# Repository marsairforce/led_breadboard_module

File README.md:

# A LED indicator module for breadboard development

I became frustrated at having to repeat the boring work of foraging parts, assembling, and then testing status LED circuits for breadboard development with digital logic circuits.

## The Problem

- Most microcontroller projects on a breadboard benefit from several LEDs to show status.
- LEDs operate at voltages lower than logic levels, so require current limiting resistors.
- LEDs typically draw about 10mA or more per LED. Sometimes it is not desirable to load the digital I/O pins from the microcontroller.
  - Quite often a single package device is not capable of sourcing the total current required for a lot of LEDs. For example a 74HC595 is typically capabale of sourcing or sinking up to 70mA. If all of their outputs are active the sum of their currents must not exceed this.
- If we use a simple current limiting resistor, we need to compute the value depending on the forward voltage of the LED and the desired voltage we are working with (today this is either 5V or 3.3V)

So in practice we would would want to set up some kind of buffer with current limiting resistors for the LEDs:

- some transistors and resistors
- or a driver IC like the ULN2803

The whole effort of building LEDs, driver circuits on a breadboard every time is error prone.

And it inconveniently takes up a lot of space on your breadboard.

So I set out to build a module that could be reused between projects.

- [Version 3](./doc/v3.md)
- [Version 2](./doc/v2.md)
- [Version 1](./doc/v1.md)

This project started of as what seemed like a simple activity but turned into a mechanism for a lot of learning.

See Also: [Transistor Theory](./doc/transistor_theory.md)

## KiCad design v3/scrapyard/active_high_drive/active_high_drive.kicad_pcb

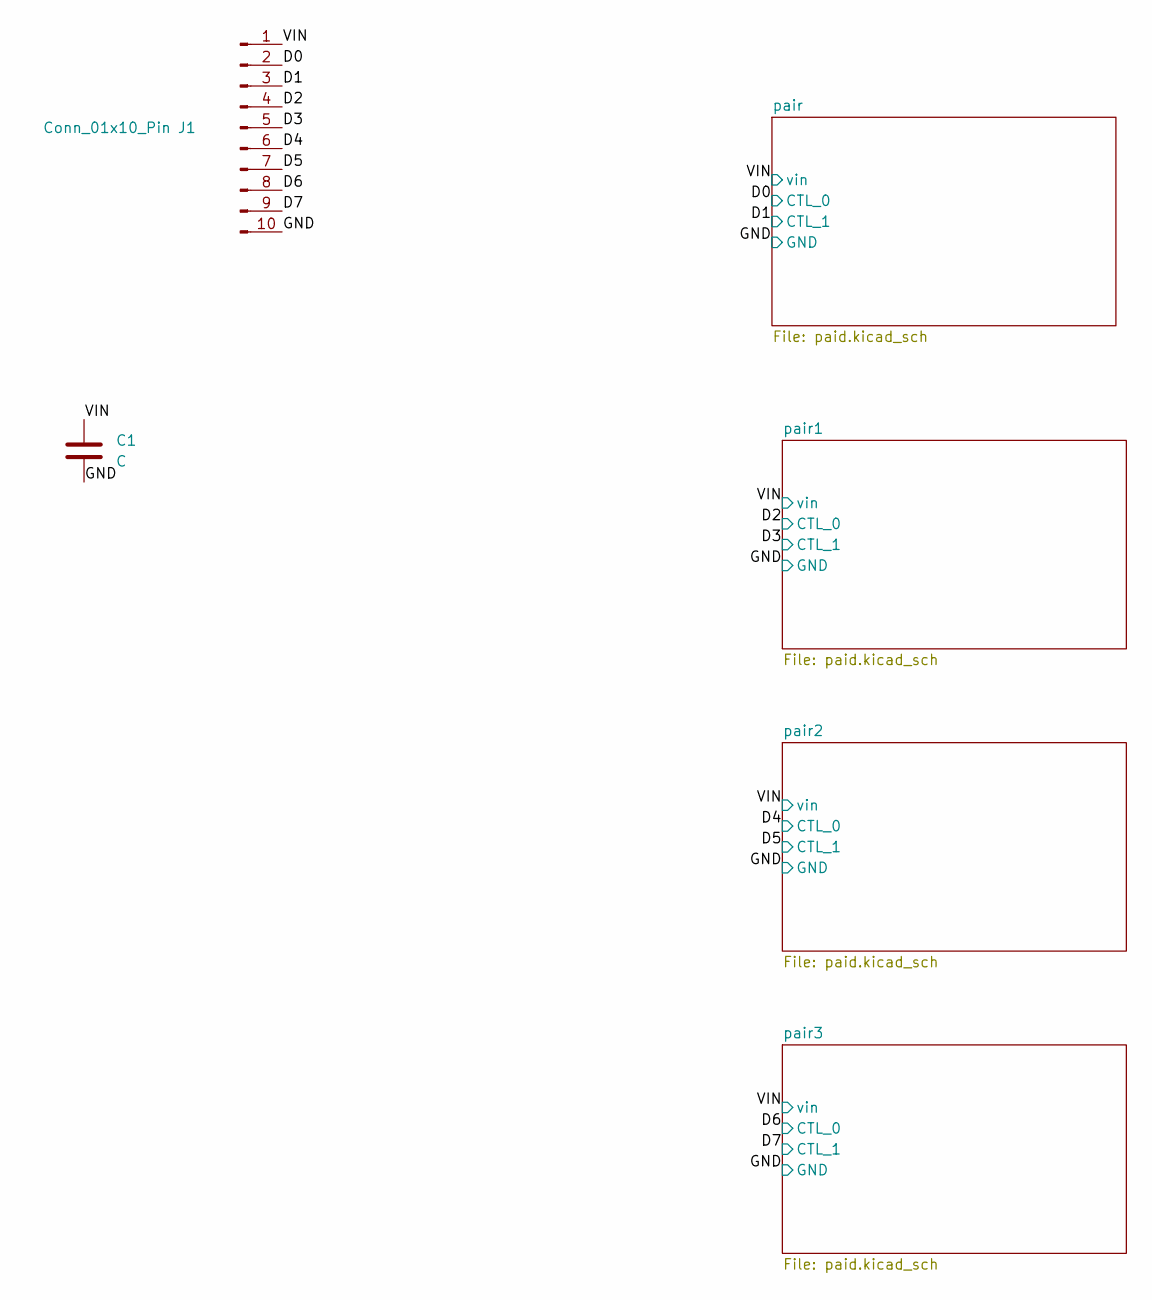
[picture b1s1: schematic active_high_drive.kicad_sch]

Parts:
C1: C; C_0603_1608Metric
J1: Conn_01x10_Pin; PinHeader_1x10_P2.54mm_Horizontal

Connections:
/D0: J1.2; also elsewhere on the board
/D1: J1.3; also elsewhere on the board
/D2: J1.4; also elsewhere on the board
/D3: J1.5; also elsewhere on the board
/D4: J1.6; also elsewhere on the board
/D5: J1.7; also elsewhere on the board
/D6: J1.8; also elsewhere on the board
/D7: J1.9; also elsewhere on the board
/GND: C1.2, J1.10; also elsewhere on the board
/VIN: C1.1, J1.1; also elsewhere on the board

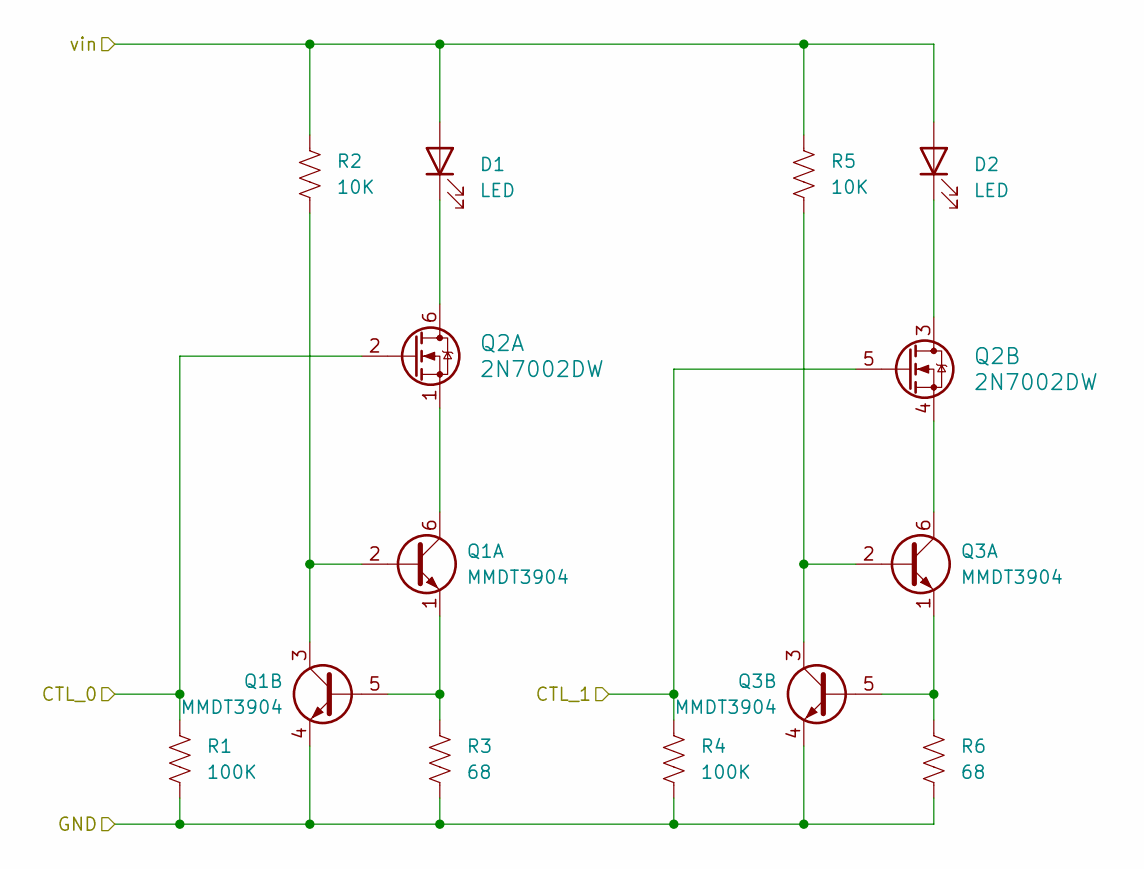
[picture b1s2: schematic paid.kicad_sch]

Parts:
D1, D2: LED; LED_0603_1608Metric
Q1, Q3: MMDT3904; SOT-363_SC-70-6
Q2: 2N7002DW; SOT-363_SC-70-6
R1, R4: 100K; R_0402_1005Metric
R2, R5: 10K; R_0402_1005Metric
R3, R6: 68; R_0402_1005Metric

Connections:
/D0: Q2.2 (G), R1.1; also elsewhere on the board
/D1: Q2.5 (G), R4.1; also elsewhere on the board
/GND: Q1.4 (E2), Q3.4 (E2), R1.2, R3.2, R4.2, R6.2; also elsewhere on the board
/VIN: D1.2 (A), D2.2 (A), R2.1, R5.1; also elsewhere on the board
unnamed: D1.1 (K), Q2.6 (D)
unnamed: D2.1 (K), Q2.3 (D)
unnamed: Q1.2 (B1), Q1.3 (C2), R2.2
unnamed: Q1.6 (C1), Q2.1 (S)
unnamed: Q1.1 (E1), Q1.5 (B2), R3.1
unnamed: Q2.4 (S), Q3.6 (C1)
unnamed: Q3.2 (B1), Q3.3 (C2), R5.2
unnamed: Q3.1 (E1), Q3.5 (B2), R6.1

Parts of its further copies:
D3, D4, D5, D6, D7, D8: LED; LED_0603_1608Metric
Q4, Q6, Q7, Q9, Q10, Q12: MMDT3904; SOT-363_SC-70-6
Q5, Q8, Q11: 2N7002DW; SOT-363_SC-70-6
R7, R10, R13, R16, R19, R22: 100K; R_0402_1005Metric
R8, R11, R14, R17, R20, R23: 10K; R_0402_1005Metric
R9, R12, R15, R18, R21, R24: 68; R_0402_1005Metric

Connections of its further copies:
/D2: Q5.2 (G), R7.1; also elsewhere on the board
/D3: Q5.5 (G), R10.1; also elsewhere on the board
/D4: Q8.2 (G), R13.1; also elsewhere on the board
/D5: Q8.5 (G), R16.1; also elsewhere on the board
/D6: Q11.2 (G), R19.1; also elsewhere on the board
/D7: Q11.5 (G), R22.1; also elsewhere on the board
/GND: Q4.4 (E2), Q6.4 (E2), Q7.4 (E2), Q9.4 (E2), Q10.4 (E2), Q12.4 (E2), R7.2, R9.2, R10.2, R12.2, R13.2, R15.2, R16.2, R18.2, R19.2, R21.2, R22.2, R24.2; also elsewhere on the board
/VIN: D3.2 (A), D4.2 (A), D5.2 (A), D6.2 (A), D7.2 (A), D8.2 (A), R8.1, R11.1, R14.1, R17.1, R20.1, R23.1; also elsewhere on the board
unnamed: D3.1 (K), Q5.6 (D)
unnamed: D4.1 (K), Q5.3 (D)
unnamed: D5.1 (K), Q8.6 (D)
unnamed: D6.1 (K), Q8.3 (D)
unnamed: D7.1 (K), Q11.6 (D)
unnamed: D8.1 (K), Q11.3 (D)
unnamed: Q4.2 (B1), Q4.3 (C2), R8.2
unnamed: Q4.6 (C1), Q5.1 (S)
unnamed: Q4.1 (E1), Q4.5 (B2), R9.1
unnamed: Q5.4 (S), Q6.6 (C1)
unnamed: Q6.2 (B1), Q6.3 (C2), R11.2
unnamed: Q6.1 (E1), Q6.5 (B2), R12.1
unnamed: Q7.2 (B1), Q7.3 (C2), R14.2
unnamed: Q7.6 (C1), Q8.1 (S)
unnamed: Q7.1 (E1), Q7.5 (B2), R15.1
unnamed: Q8.4 (S), Q9.6 (C1)
unnamed: Q9.2 (B1), Q9.3 (C2), R17.2
unnamed: Q9.1 (E1), Q9.5 (B2), R18.1
unnamed: Q10.2 (B1), Q10.3 (C2), R20.2
unnamed: Q10.6 (C1), Q11.1 (S)
unnamed: Q10.1 (E1), Q10.5 (B2), R21.1
unnamed: Q11.4 (S), Q12.6 (C1)
unnamed: Q12.2 (B1), Q12.3 (C2), R23.2
unnamed: Q12.1 (E1), Q12.5 (B2), R24.1

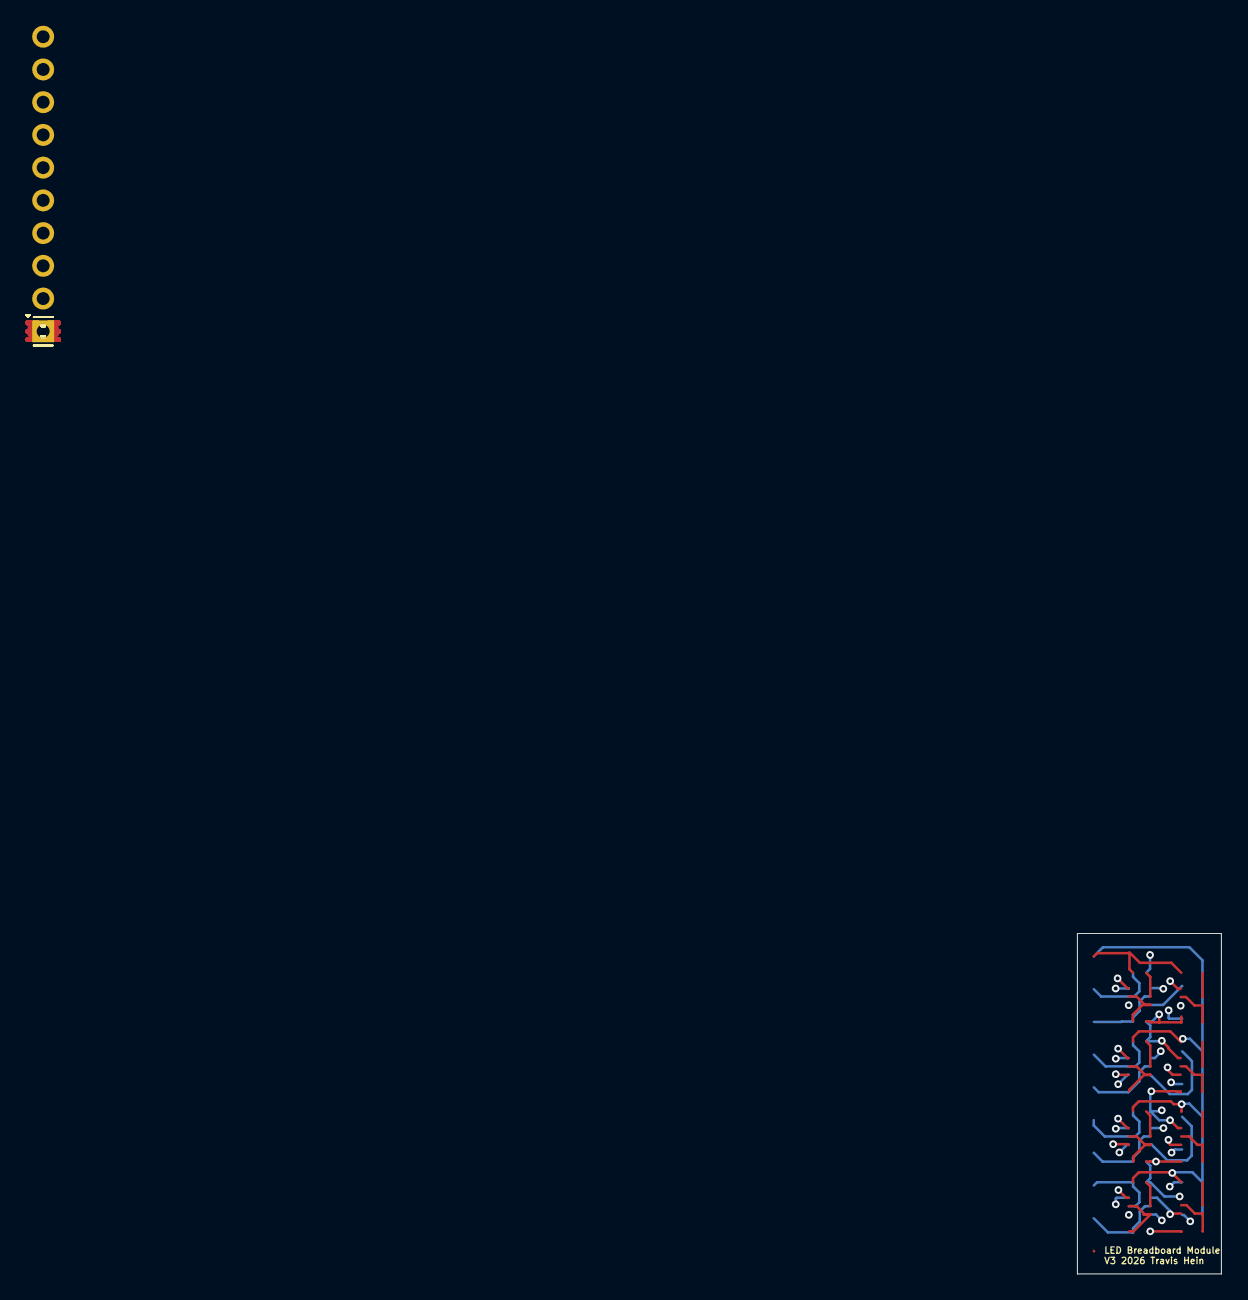
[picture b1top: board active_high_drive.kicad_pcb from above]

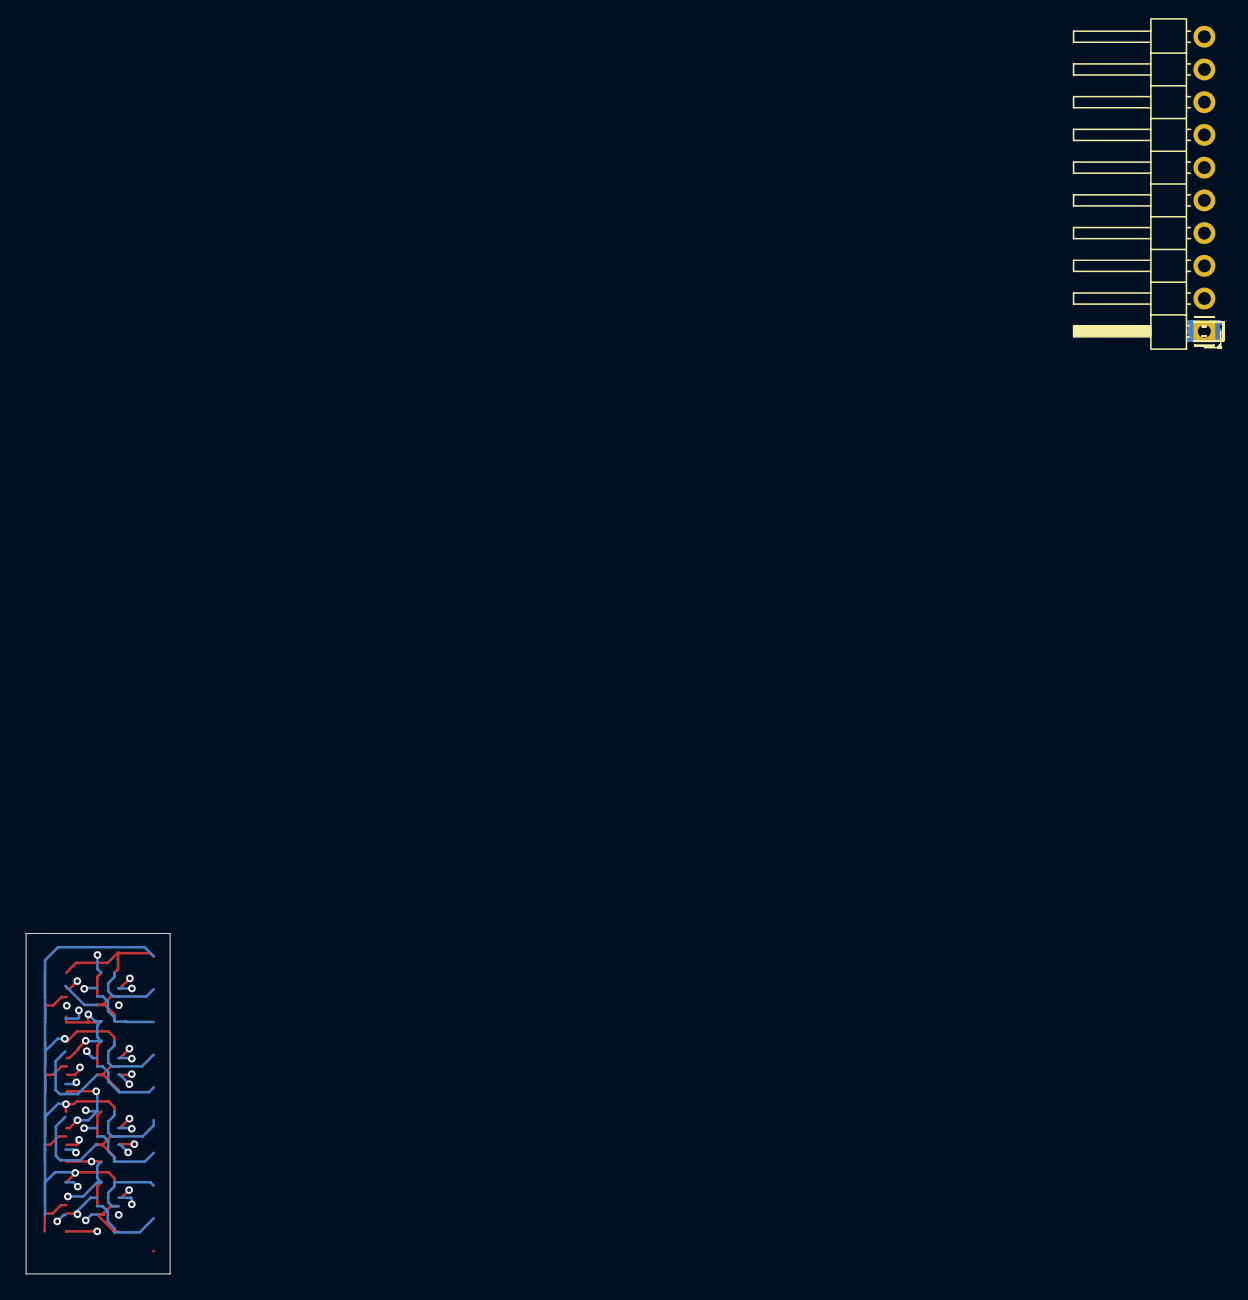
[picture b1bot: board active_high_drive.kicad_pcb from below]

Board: 4 copper layers, 11.2 x 26.4 mm, 46 parts (21 on the bottom side), 42 nets.

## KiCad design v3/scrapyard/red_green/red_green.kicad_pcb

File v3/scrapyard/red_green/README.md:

# A red-green LED module for breadboard

This makes use of a bi-color LED. This is a two terminal device. If you supply power one direction it shines red. But if you revese the polarity it shines green.

I wanted to create an easy to use module that lets you change the color and have a mode where there was no output at all (off)

Because each diode has its own different forward voltage the challenge is to use a different resistor or limiting the current. Otherwise the green LED would appear dimmer or the red would appear brighter.  If I just use the constant current sink (or source) this should solve the current problem.

And then a H bridge approach to power the led in alternate directions. Like a DC motor.
But then this requires several small transistors. A first design reduced the package count by using packages with two devices in them.
This had a nice side effect of learning about the SOT-363 package. But I was able to furrher simplify this using a single H bridge IC.
Yes. it is rediculous and over engineered. But it is functional, not very expensive with available parts, and not very much board space. I can see myself adding this indicator to arbitrary projects now.

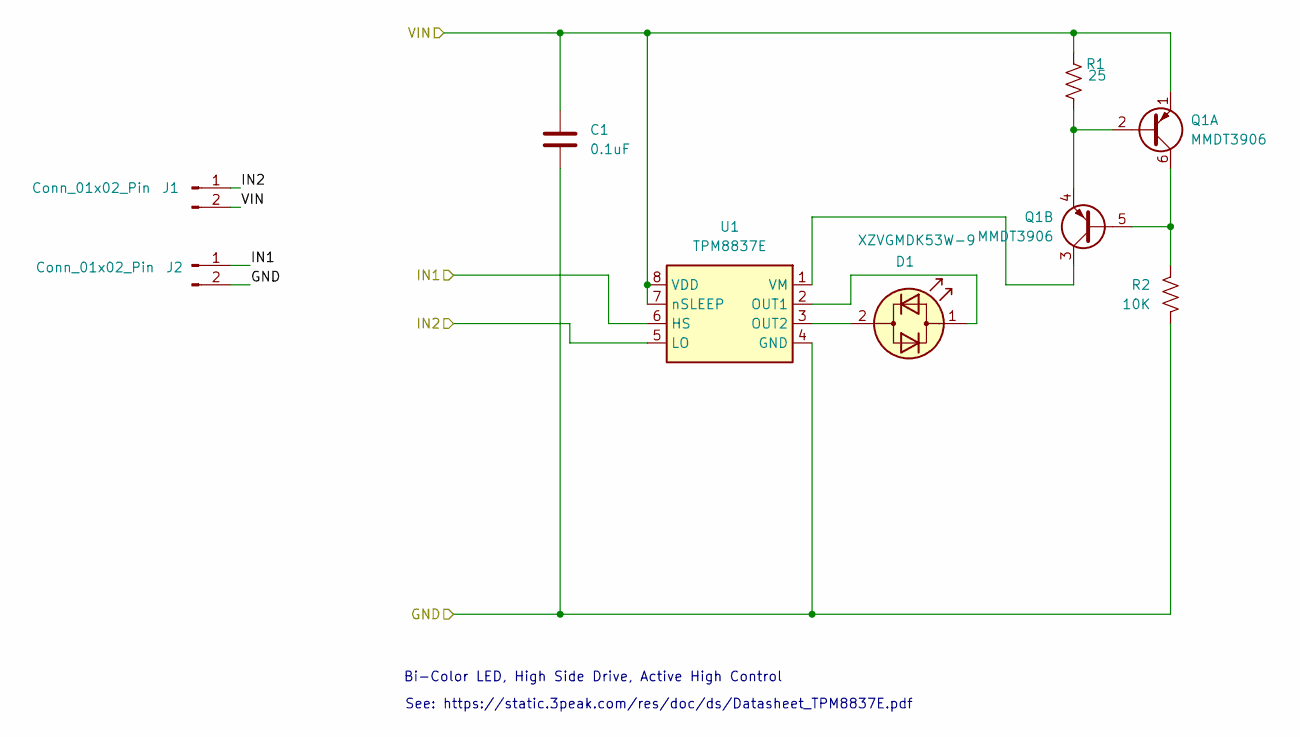
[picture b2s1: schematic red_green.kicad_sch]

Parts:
C1: 0.1uF; C_0603_1608Metric
D1: XZVGMDK53W-9; LED_0603_1608Metric
J1, J2: Conn_01x02_Pin; PinHeader_1x02_P2.54mm_Vertical
Q1: MMDT3906; SOT-363_SC-70-6
R1: 25; R_0603_1608Metric
R2: 10K; R_0603_1608Metric
U1: TPM8837E; DFN-8-1EP_2x2mm_P0.5mm_EP0.6x1.2mm

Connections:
/GND: C1.2, J2.2, R2.2, U1.4 (GND)
/IN1: J2.1, U1.6 (HS)
/IN2: J1.1, U1.5 (LO)
/VIN: C1.1, J1.2, Q1.1 (E1), R1.1, U1.7 (nSLEEP), U1.8 (VDD)
unnamed: D1.2 (AK), U1.3 (OUT2)
unnamed: D1.1 (KA), U1.2 (OUT1)
unnamed: Q1.2 (B1), Q1.4 (E2), R1.2
unnamed: Q1.5 (B2), Q1.6 (C1), R2.1
unnamed: Q1.3 (C2), U1.1 (VM)

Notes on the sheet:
See: https://static.3peak.com/res/doc/ds/Datasheet_TPM8837E.pdf
Bi-Color LED, High Side Drive, Active High Control

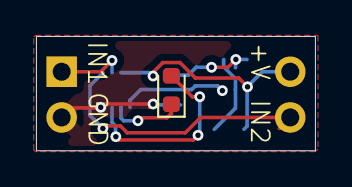
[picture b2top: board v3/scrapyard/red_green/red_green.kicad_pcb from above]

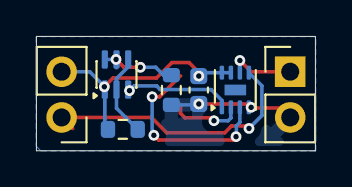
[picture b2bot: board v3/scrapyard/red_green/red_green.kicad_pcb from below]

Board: 2 copper layers, 15.5 x 6.4 mm, 8 parts (7 on the bottom side), 9 nets.

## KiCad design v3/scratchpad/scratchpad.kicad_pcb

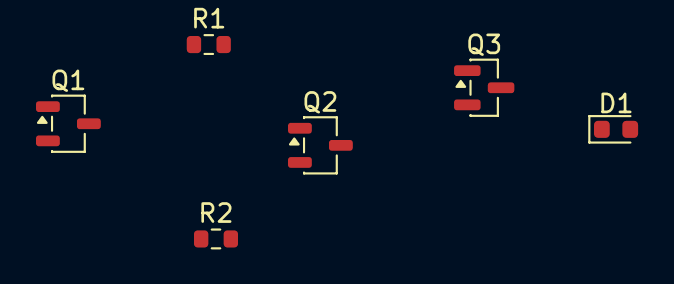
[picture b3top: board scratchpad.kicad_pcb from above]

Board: 2 copper layers, 6 parts (0 on the bottom side), 6 nets, no tracks yet.

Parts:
D1: LIST-C191K; LED_0603_1608Metric
Q1, Q2: MMTB3904; SOT-23-3
Q3: BSS138; SOT-23
R1: 10K; R_0603_1608Metric
R2: 68; R_0603_1608Metric

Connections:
/V+: D1.2 (A), R1.2
/V-: Q1.2 (E), R2.2
unnamed: D1.1 (K), Q2.3 (C)
unnamed: Q1.1 (B), Q3.2 (S), R2.1
unnamed: Q1.3 (C), Q2.1 (B), R1.1
unnamed: Q2.2 (E), Q3.3 (D)

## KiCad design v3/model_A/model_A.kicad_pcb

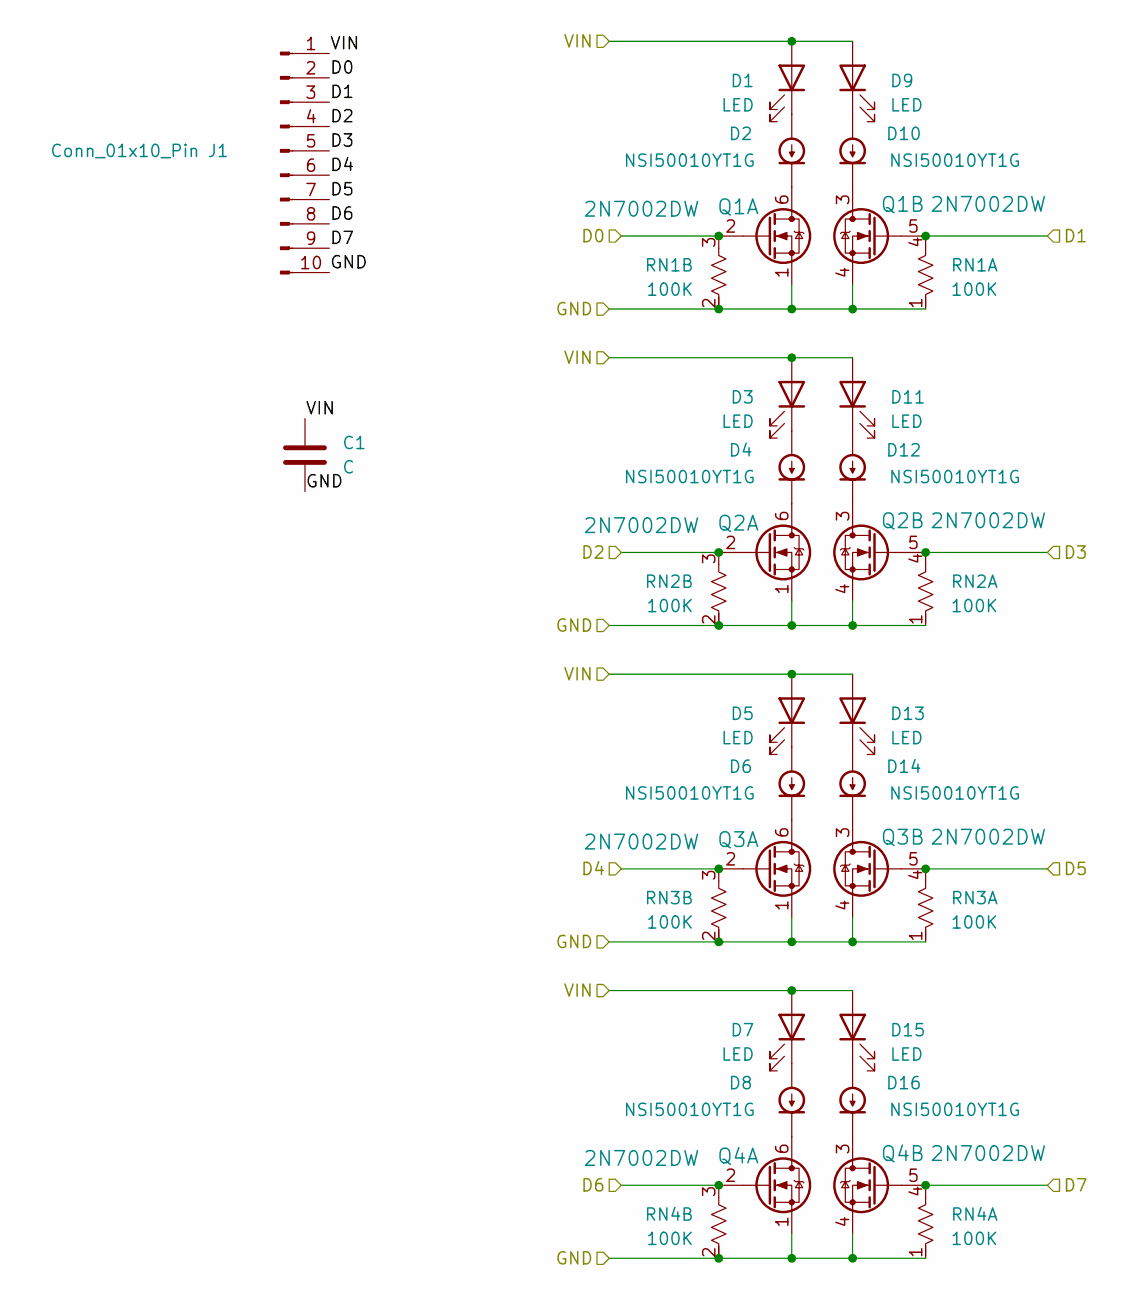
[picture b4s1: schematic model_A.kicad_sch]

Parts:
C1: C; C_0603_1608Metric
D1, D3, D5, D7, D9, D11, D13, D15: LED; LED_0603_1608Metric
D2, D4, D6, D8, D10, D12, D14, D16: NSI50010YT1G; D_SOD-123
J1: Conn_01x10_Pin; PinHeader_1x10_P2.54mm_Horizontal
Q1, Q2, Q3, Q4: 2N7002DW; SOT-363_SC-70-6
RN1, RN2, RN3, RN4: 100K; R_Array_Convex_2x0402

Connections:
/D0: J1.2, Q1.2 (G), RN1.3 (R1)
/D1: J1.3, Q1.5 (G), RN1.4 (R1)
/D2: J1.4, Q2.2 (G), RN2.3 (R1)
/D3: J1.5, Q2.5 (G), RN2.4 (R1)
/D4: J1.6, Q3.2 (G), RN3.3 (R1)
/D5: J1.7, Q3.5 (G), RN3.4 (R1)
/D6: J1.8, Q4.2 (G), RN4.3 (R1)
/D7: J1.9, Q4.5 (G), RN4.4 (R1)
/GND: C1.2, J1.10, Q1.1 (S), Q1.4 (S), Q2.1 (S), Q2.4 (S), Q3.1 (S), Q3.4 (S), Q4.1 (S), Q4.4 (S), RN1.1 (R1.2), RN1.2 (R2.2), RN2.1 (R1.2), RN2.2 (R2.2), RN3.1 (R1.2), RN3.2 (R2.2), RN4.1 (R1.2), RN4.2 (R2.2)
/VIN: C1.1, D1.2 (A), D3.2 (A), D5.2 (A), D7.2 (A), D9.2 (A), D11.2 (A), D13.2 (A), D15.2 (A), J1.1
unnamed: D1.1 (K), D2.2 (A)
unnamed: D2.1 (K), Q1.6 (D)
unnamed: D3.1 (K), D4.2 (A)
unnamed: D4.1 (K), Q2.6 (D)
unnamed: D5.1 (K), D6.2 (A)
unnamed: D6.1 (K), Q3.6 (D)
unnamed: D7.1 (K), D8.2 (A)
unnamed: D8.1 (K), Q4.6 (D)
unnamed: D9.1 (K), D10.2 (A)
unnamed: D10.1 (K), Q1.3 (D)
unnamed: D11.1 (K), D12.2 (A)
unnamed: D12.1 (K), Q2.3 (D)
unnamed: D13.1 (K), D14.2 (A)
unnamed: D14.1 (K), Q3.3 (D)
unnamed: D15.1 (K), D16.2 (A)
unnamed: D16.1 (K), Q4.3 (D)

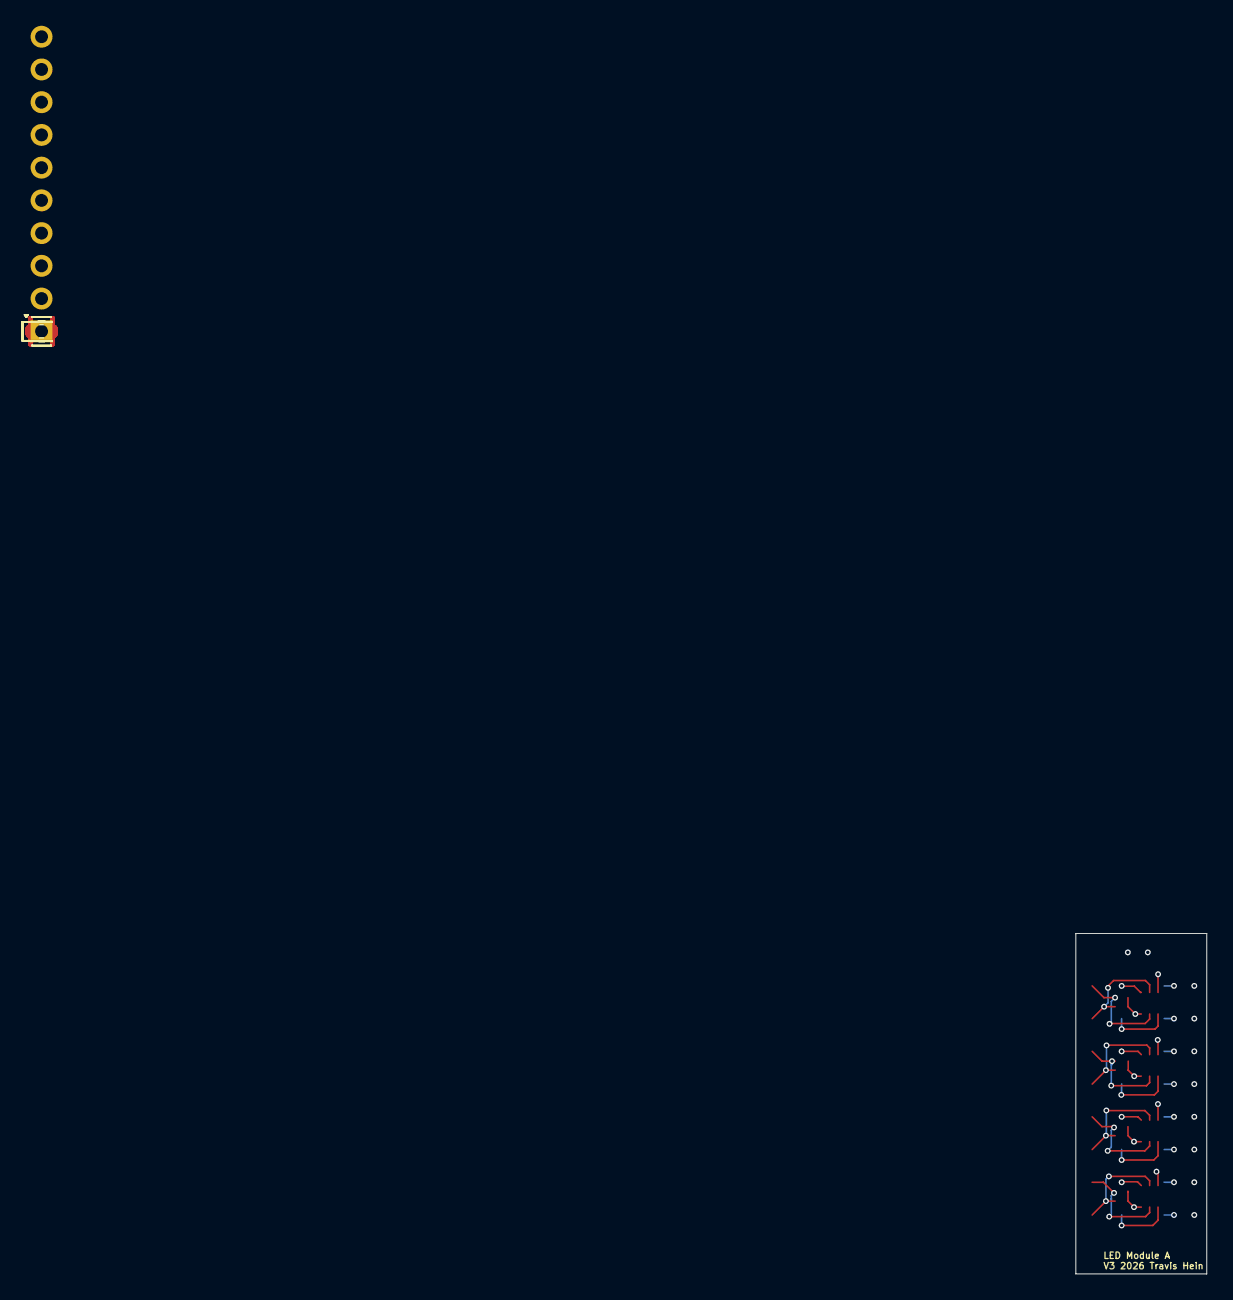
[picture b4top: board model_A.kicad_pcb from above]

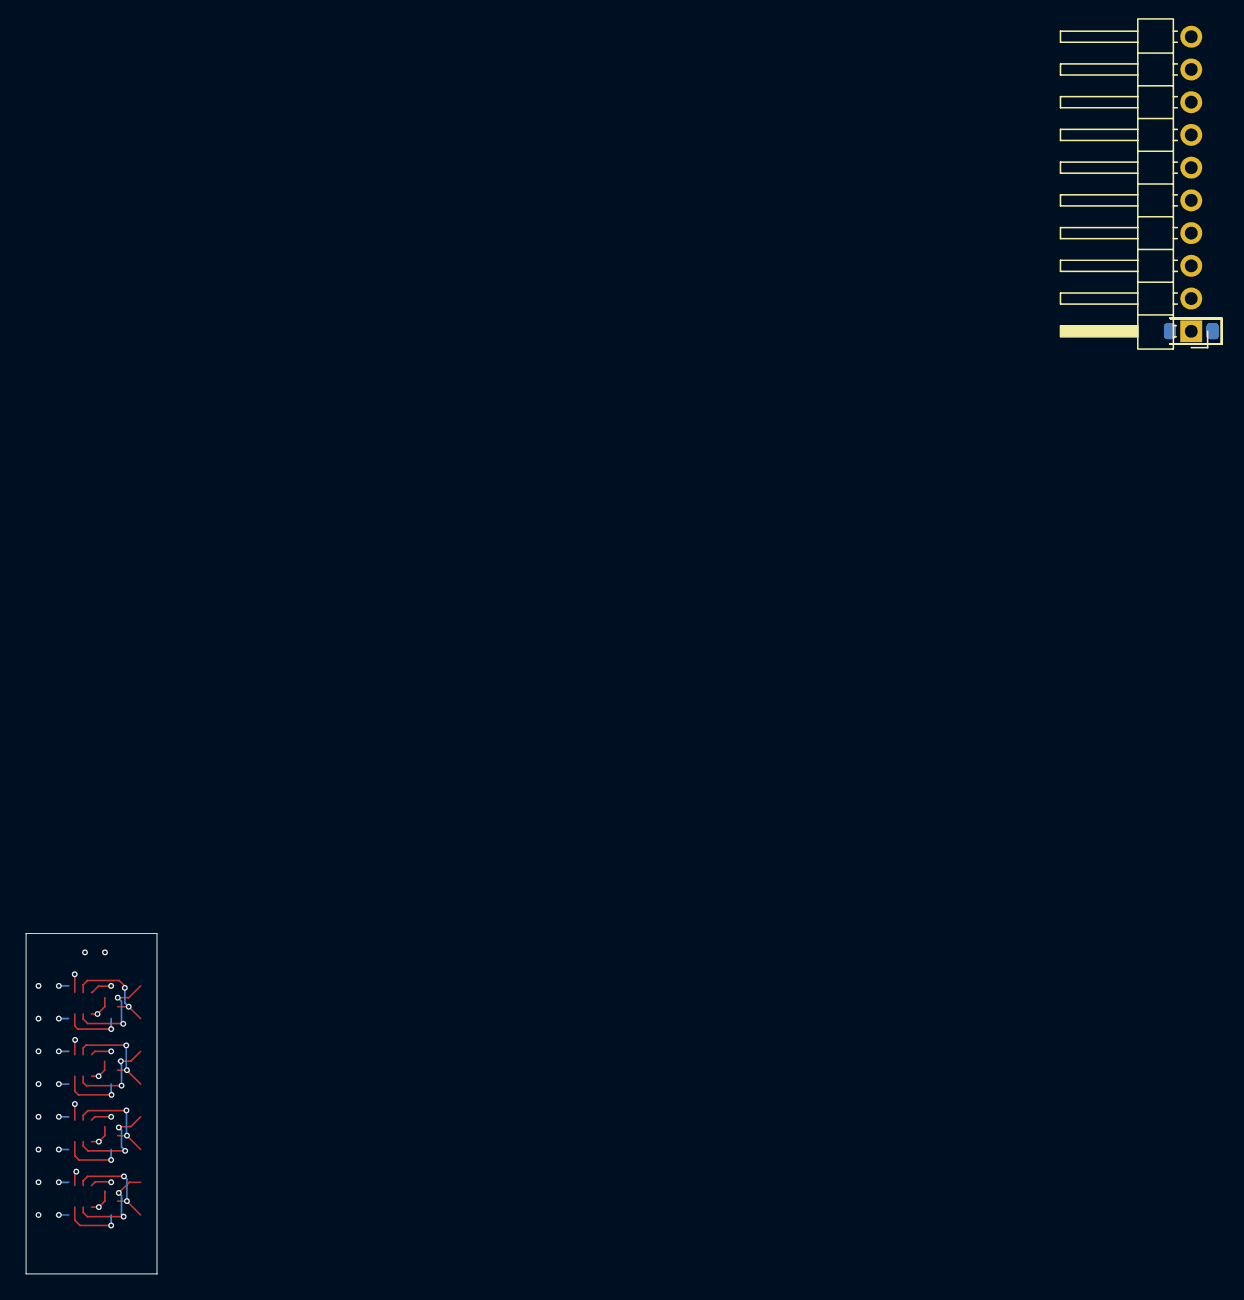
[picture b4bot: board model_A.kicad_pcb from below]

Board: 4 copper layers, 10.2 x 26.4 mm, 26 parts (9 on the bottom side), 26 nets.

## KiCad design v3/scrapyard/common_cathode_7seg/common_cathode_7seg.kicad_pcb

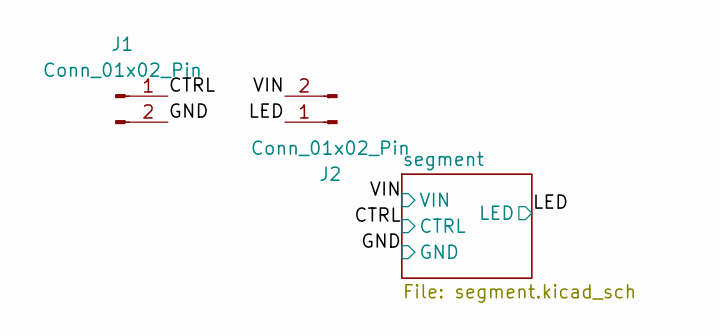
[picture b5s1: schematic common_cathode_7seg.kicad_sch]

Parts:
J1, J2: Conn_01x02_Pin; Conn_Mill-Max_0508_1x02_P2.54mm

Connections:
/CTRL: J1.1; also elsewhere on the board
/GND: J1.2; also elsewhere on the board
/LED: J2.1; also elsewhere on the board
/VIN: J2.2; also elsewhere on the board

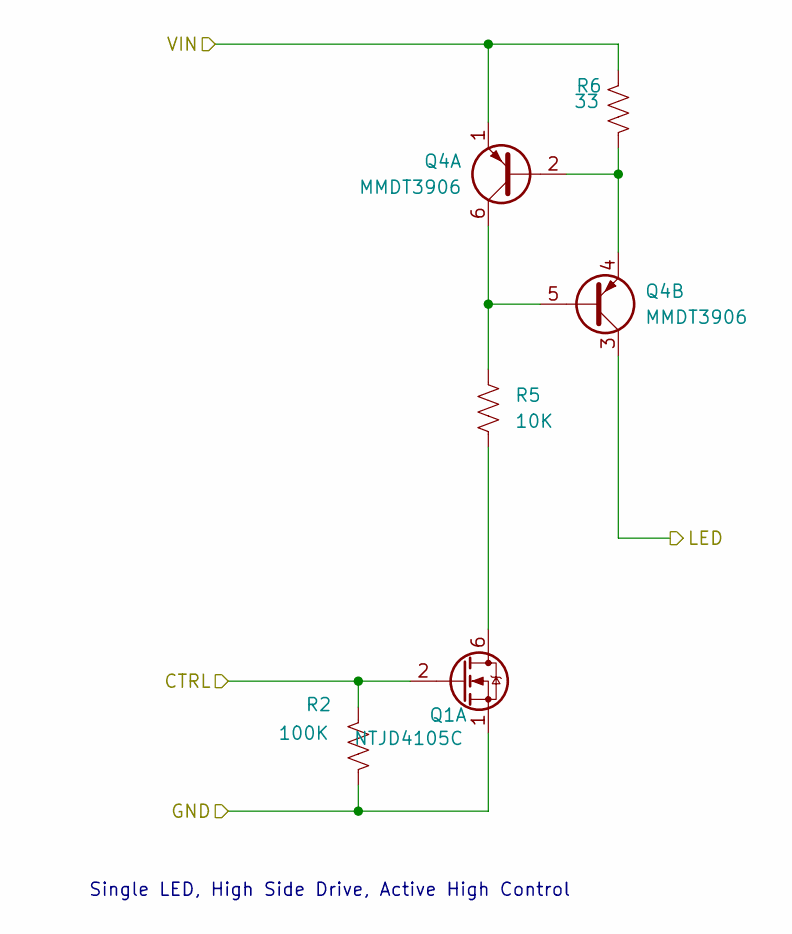
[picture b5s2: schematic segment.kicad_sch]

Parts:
Q1: NTJD4105C; SOT-363_SC-70-6
Q4: MMDT3906; SOT-363_SC-70-6
R2: 100K; R_0603_1608Metric
R5: 10K; R_0603_1608Metric
R6: 33; R_0603_1608Metric

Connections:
/CTRL: Q1.2 (G), R2.1; also elsewhere on the board
/GND: Q1.1 (S), R2.2; also elsewhere on the board
/LED: Q4.3 (C2); also elsewhere on the board
/VIN: Q4.1 (E1), R6.1; also elsewhere on the board
unnamed: Q1.6 (D), R5.2
unnamed: Q4.2 (B1), Q4.4 (E2), R6.2
unnamed: Q4.5 (B2), Q4.6 (C1), R5.1

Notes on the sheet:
Single LED, High Side Drive, Active High Control

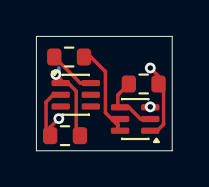
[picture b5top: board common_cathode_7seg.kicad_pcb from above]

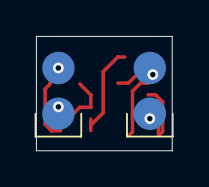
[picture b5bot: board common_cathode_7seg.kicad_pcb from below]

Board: 2 copper layers, 7.5 x 6.4 mm, 7 parts (2 on the bottom side), 7 nets.

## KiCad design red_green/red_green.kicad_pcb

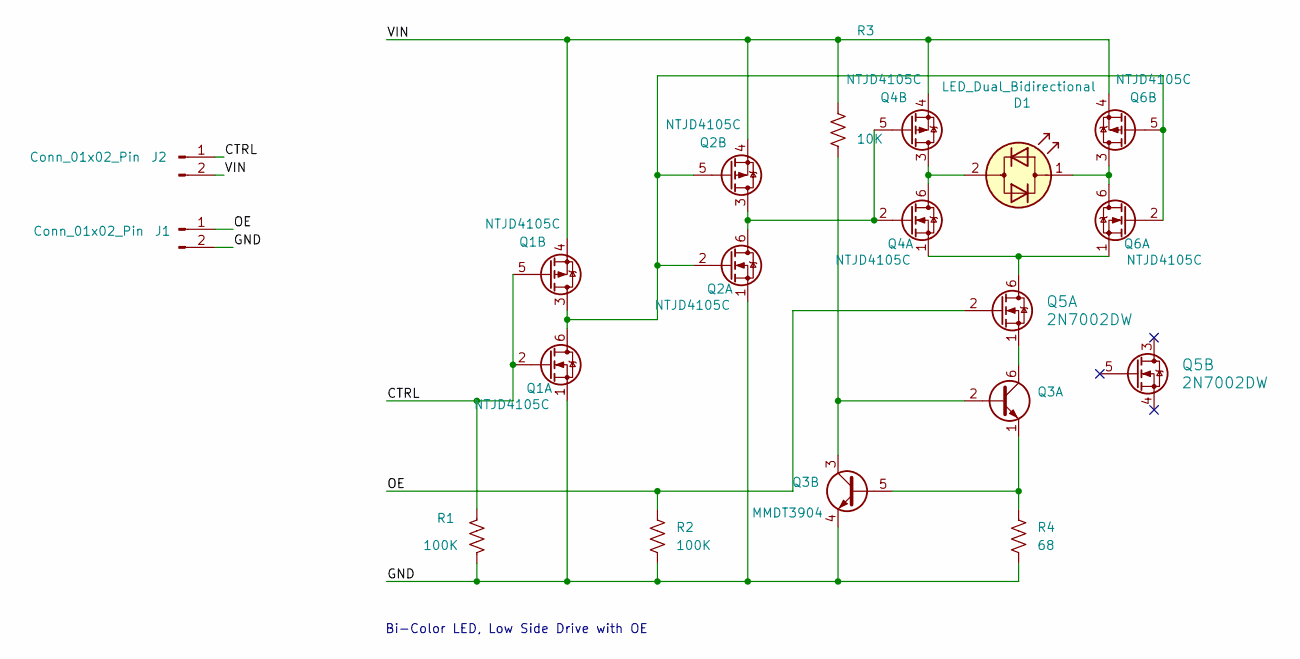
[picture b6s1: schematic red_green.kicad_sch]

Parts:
D1: LED_Dual_Bidirectional; LED_0603_1608Metric
J1, J2: Conn_01x02_Pin; PinHeader_1x02_P2.54mm_Vertical
Q1, Q2, Q4, Q6: NTJD4105C; SOT-363_SC-70-6
Q3: MMDT3904; SOT-363_SC-70-6
Q5: 2N7002DW; SOT-363_SC-70-6
R1, R2: 100K; R_0603_1608Metric
R3: 10K; R_0603_1608Metric
R4: 68; R_0603_1608Metric

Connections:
/CTRL: J2.1, Q1.2 (G), Q1.5 (G), R1.1
/GND: J1.2, Q1.1 (S), Q2.1 (S), Q3.4 (E2), R1.2, R2.2, R4.2
/OE: J1.1, Q5.2 (G), R2.1
/VIN: J2.2, Q1.4 (S), Q2.4 (S), Q4.4 (S), Q6.4 (S), R3.1
unnamed: D1.2 (AK), Q4.3 (D), Q4.6 (D)
unnamed: D1.1 (KA), Q6.3 (D), Q6.6 (D)
unnamed: Q1.3 (D), Q1.6 (D), Q2.2 (G), Q2.5 (G), Q6.2 (G), Q6.5 (G)
unnamed: Q2.3 (D), Q2.6 (D), Q4.2 (G), Q4.5 (G)
unnamed: Q3.2 (B1), Q3.3 (C2), R3.2
unnamed: Q3.6 (C1), Q5.1 (S)
unnamed: Q3.1 (E1), Q3.5 (B2), R4.1
unnamed: Q4.1 (S), Q5.6 (D), Q6.1 (S)

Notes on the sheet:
Bi-Color LED, Low Side Drive with OE

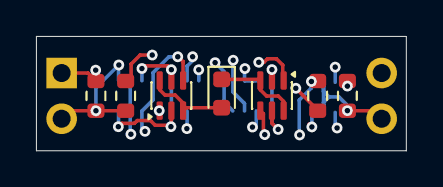
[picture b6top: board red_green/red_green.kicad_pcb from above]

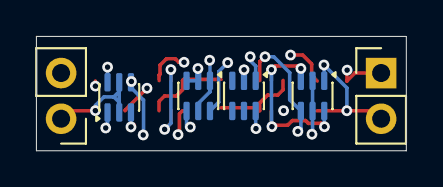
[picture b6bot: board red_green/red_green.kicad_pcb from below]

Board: 4 copper layers, 20.5 x 6.4 mm, 13 parts (6 on the bottom side), 12 nets.

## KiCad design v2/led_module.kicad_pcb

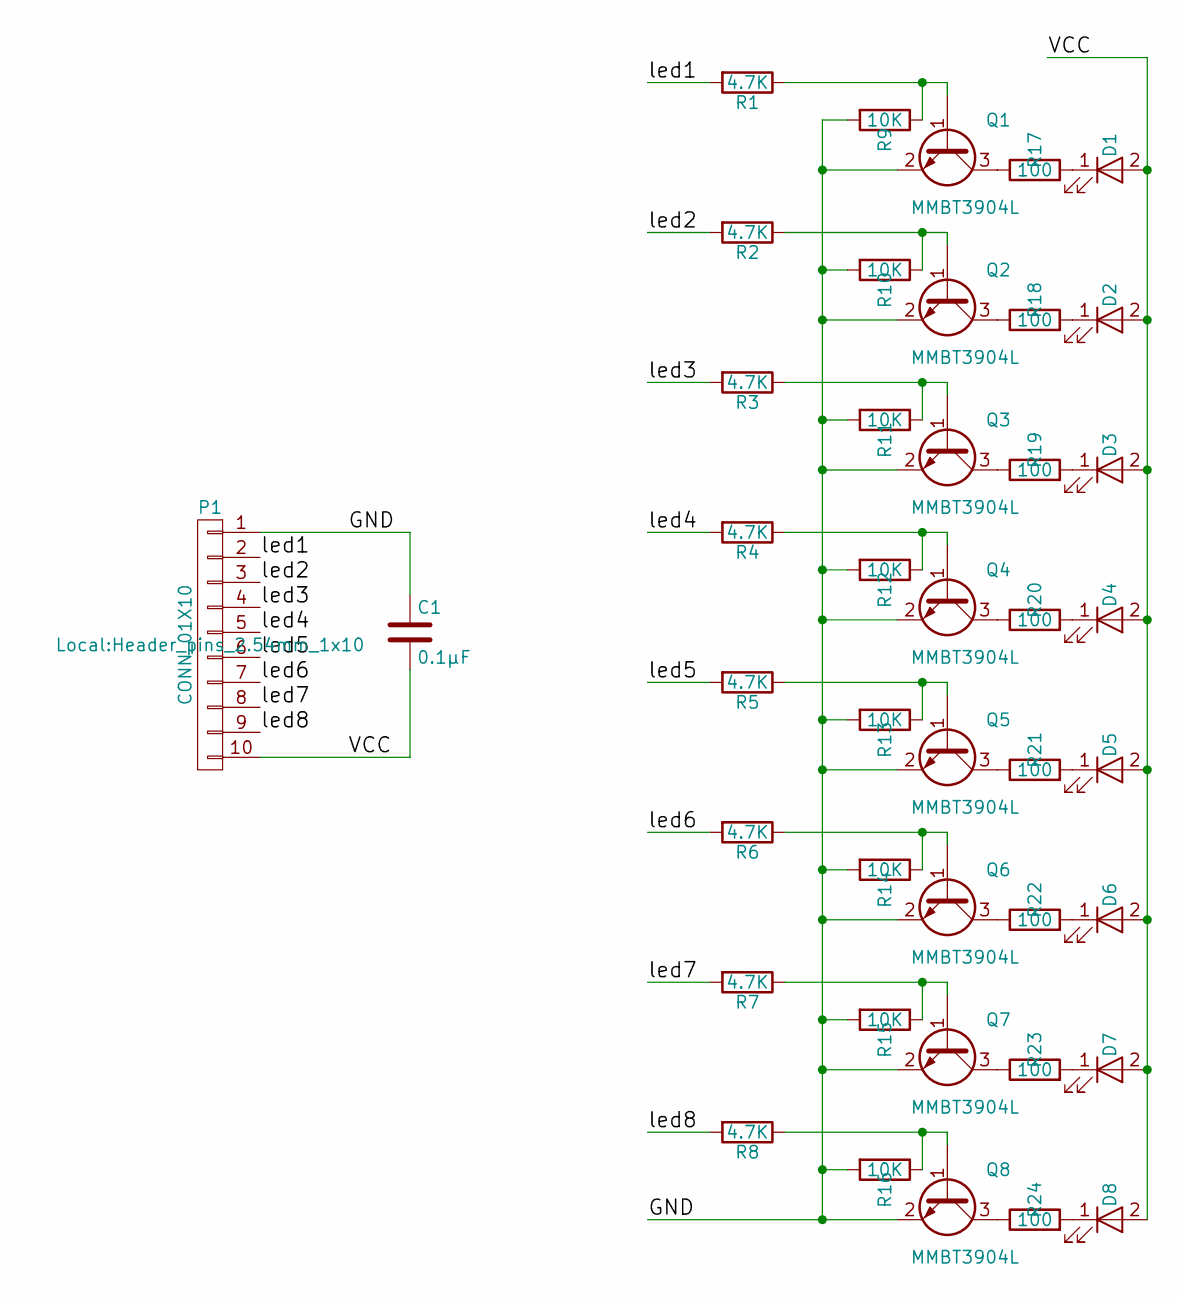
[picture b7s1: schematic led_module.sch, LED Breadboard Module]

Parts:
C1: 0.1µF; C_0603
D1, D2, D3, D4, D5, D6, D7, D8: LTST-C190EKT; LED_0603
P1: CONN_01X10; Header_pins_2.54mm_1x10
Q1, Q2, Q3, Q4, Q5, Q6, Q7, Q8: MMBT3904L; SOT-23
R1, R2, R3, R4, R5, R6, R7, R8: 4.7K; R_0603
R9, R10, R11, R12, R13, R14, R15, R16: 10K; R_0603
R17, R18, R19, R20, R21, R22, R23, R24: 100; R_0603

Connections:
/GND: C1.1, P1.1, Q1.2 (E), Q2.2 (E), Q3.2 (E), Q4.2 (E), Q5.2 (E), Q6.2 (E), Q7.2 (E), Q8.2 (E), R9.2, R10.2, R11.2, R12.2, R13.2, R14.2, R15.2, R16.2
/VCC: C1.2, D1.2 (A), D2.2 (A), D3.2 (A), D4.2 (A), D5.2 (A), D6.2 (A), D7.2 (A), D8.2 (A), P1.10
/led1: P1.2, R1.2
/led2: P1.3, R2.2
/led3: P1.4, R3.2
/led4: P1.5, R4.2
/led5: P1.6, R5.2
/led6: P1.7, R6.2
/led7: P1.8, R7.2
/led8: P1.9, R8.2
unnamed: D1.1 (K), R17.2
unnamed: D2.1 (K), R18.2
unnamed: D3.1 (K), R19.2
unnamed: D4.1 (K), R20.2
unnamed: D5.1 (K), R21.2
unnamed: D6.1 (K), R22.2
unnamed: D7.1 (K), R23.2
unnamed: D8.1 (K), R24.2
unnamed: Q1.1 (B), R1.1, R9.1
unnamed: Q1.3 (C), R17.1
unnamed: Q2.1 (B), R2.1, R10.1
unnamed: Q2.3 (C), R18.1
unnamed: Q3.1 (B), R3.1, R11.1
unnamed: Q3.3 (C), R19.1
unnamed: Q4.1 (B), R4.1, R12.1
unnamed: Q4.3 (C), R20.1
unnamed: Q5.1 (B), R5.1, R13.1
unnamed: Q5.3 (C), R21.1
unnamed: Q6.1 (B), R6.1, R14.1
unnamed: Q6.3 (C), R22.1
unnamed: Q7.1 (B), R7.1, R15.1
unnamed: Q7.3 (C), R23.1
unnamed: Q8.1 (B), R8.1, R16.1
unnamed: Q8.3 (C), R24.1

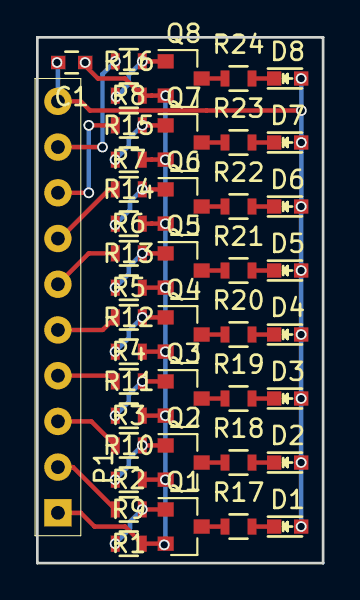
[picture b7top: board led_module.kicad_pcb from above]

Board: 2 copper layers, 15.9 x 29.2 mm, 42 parts (0 on the bottom side), 34 nets.

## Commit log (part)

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2017-01-12 add README
2018-01-19 import files previously in the kicad proect folder
2018-05-11 update documentation
2020-09-28 check out and rescue symbols
2020-09-28 update description
    add picture of v1
2021-04-26 start a v3 design
2026-06-30 local mods
